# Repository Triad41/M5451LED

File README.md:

# M5451LED is an Arduino Shield with an 8 digit LED display and 14 additional Outputs. It is based on the M5451 40 pin Dip IC. The IC basically works as a shift register with 35 output lines. Each line can sink about 25mA which allows it to directly drive LEDs. 21 Lines are used for the display segments and digit selection in a multiplexed fashion. The additional 14 outputs are available on a 20 postion header allowing expansion of the shield. The shield uses only 2 data lines from the arduino for (clock and data). The M5451.zip file is the Arduino libaray and 2 example programs for the shield. The first is a straight loop approach for updating the display, the second is an itnerrupt based approach for updating the display.

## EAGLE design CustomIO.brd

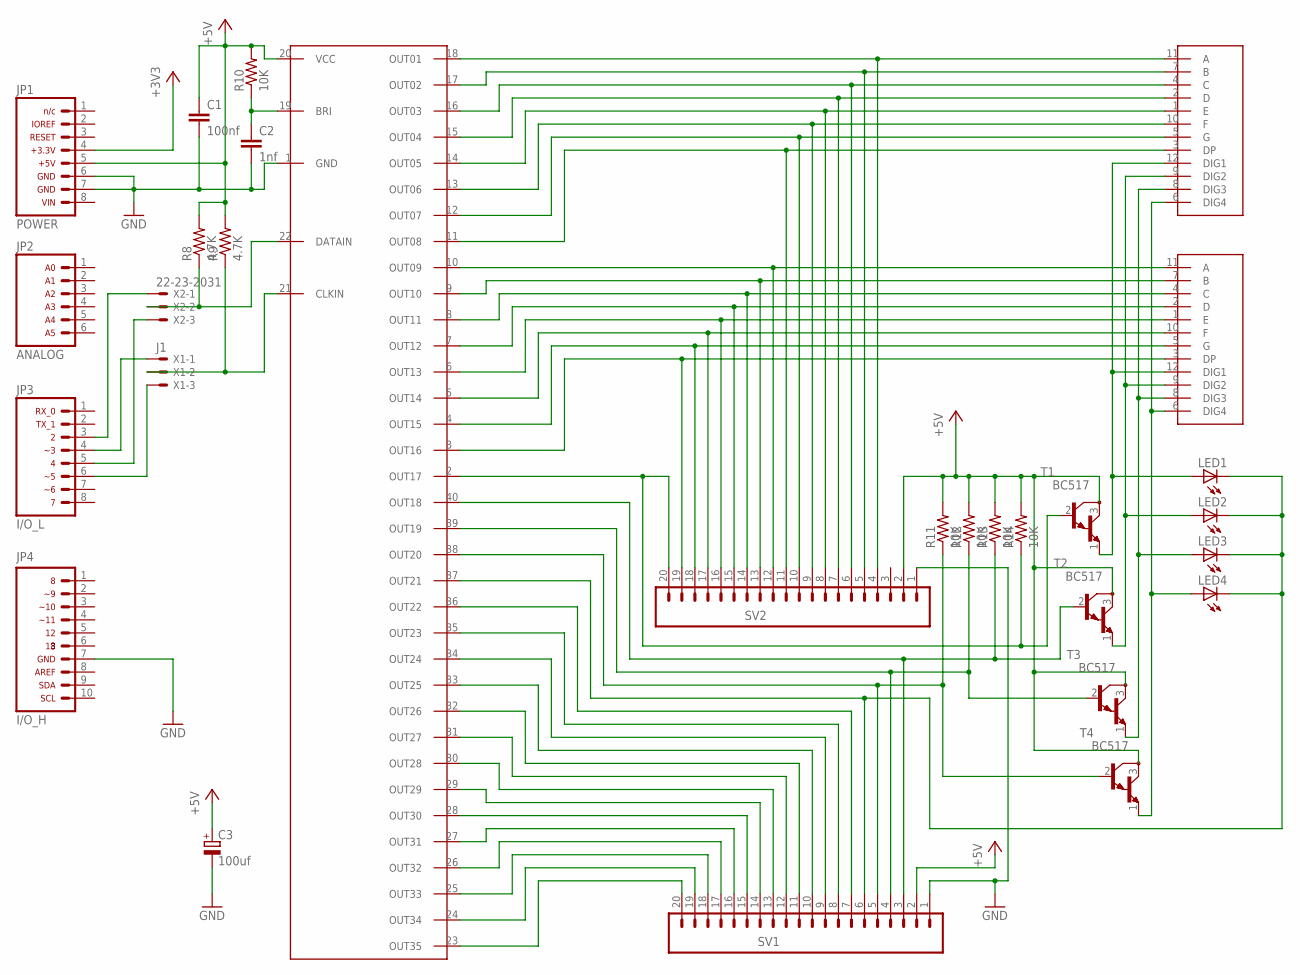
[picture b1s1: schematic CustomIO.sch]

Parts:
C1: 100nf; C2.5-4
C2: 1nf; C5B2.5
C3: 100uf; E2,5-7---100UF
JP1: ARDUINO_CONN-POWERSIP; CONN-1X08
JP2: ARDUINO_CONN-ANALOGSIP; CONN-1X06
JP3: ARDUINO_CONN-IO_LSIP; CONN-1X08
JP4: ARDUINO_CONN-IO_HSIP; CONN-1X10
LED1, LED2, LED3, LED4: LED3MM; HLMP-D105
R8, R9: 4.7K; AXIAL-0.3-KIT
R10, R11, R12, R13, R14: 10K; AXIAL-0.3-KIT
SV1, SV2: MA10-2
T1, T2, T3, T4: BC517; TO92
U$1: ST-M5451PDIP40; DIL40
U$2, U$3: LDS-3461BXTHURHOLE; LDS-3461BX
X1: J1; 22-23-2031
X2: 22-23-2031

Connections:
+3V3: JP1.4
+5V: C1.1, C3.+, JP1.5, R8.P$2 (2), R9.P$2 (2), R10.P$2 (2), R11.P$2 (2), R12.P$2 (2), R13.P$2 (2), R14.P$2 (2), SV1.2, SV2.2, T1.3 (C), T2.3 (C), T3.3 (C), T4.3 (C), U$1.20 (VCC)
GND: C1.2, C2.2, C3.-, JP1.6, JP1.7, JP4.7, SV1.1, SV2.1, U$1.1 (GND)
unnamed: SV2.4, U$1.18 (OUT01), U$2.11 (A)
unnamed: SV2.5, U$1.17 (OUT02), U$2.7 (B)
unnamed: SV2.6, U$1.16 (OUT03), U$2.4 (C)
unnamed: SV2.7, U$1.15 (OUT04), U$2.2 (D)
unnamed: SV2.8, U$1.14 (OUT05), U$2.1 (E)
unnamed: SV2.9, U$1.13 (OUT06), U$2.10 (F)
unnamed: SV2.10, U$1.12 (OUT07), U$2.5 (G)
unnamed: SV2.11, U$1.11 (OUT08), U$2.3 (DP)
unnamed: LED4.A, T4.1 (E), U$2.6 (DIG4), U$3.6 (DIG4)
unnamed: LED3.A, T3.1 (E), U$2.8 (DIG3), U$3.8 (DIG3)
unnamed: LED2.A, T2.1 (E), U$2.9 (DIG2), U$3.9 (DIG2)
unnamed: LED1.A, T1.1 (E), U$2.12 (DIG1), U$3.12 (DIG1)
unnamed: SV2.12, U$1.10 (OUT09), U$3.11 (A)
unnamed: SV2.13, U$1.9 (OUT10), U$3.7 (B)
unnamed: SV2.14, U$1.8 (OUT11), U$3.4 (C)
unnamed: SV2.15, U$1.7 (OUT12), U$3.2 (D)
unnamed: SV2.16, U$1.6 (OUT13), U$3.1 (E)
unnamed: SV2.17, U$1.5 (OUT14), U$3.10 (F)
unnamed: SV2.18, U$1.4 (OUT15), U$3.5 (G)
unnamed: SV2.19, U$1.3 (OUT16), U$3.3 (DP)
unnamed: SV1.20, U$1.23 (OUT35)
unnamed: SV1.19, U$1.24 (OUT34)
unnamed: SV1.18, U$1.25 (OUT33)
unnamed: SV1.17, U$1.26 (OUT32)
unnamed: SV1.16, U$1.27 (OUT31)
unnamed: SV1.15, U$1.28 (OUT30)
unnamed: SV1.14, U$1.29 (OUT29)
unnamed: SV1.13, U$1.30 (OUT28)
unnamed: SV1.12, U$1.31 (OUT27)
unnamed: SV1.11, U$1.32 (OUT26)
unnamed: SV1.10, U$1.33 (OUT25)
unnamed: SV1.9, U$1.34 (OUT24)
unnamed: SV1.8, U$1.35 (OUT23)
unnamed: SV1.7, U$1.36 (OUT22)
unnamed: LED1.K (C), LED2.K (C), LED3.K (C), LED4.K (C), SV1.6, U$1.37 (OUT21)
unnamed: R11.P$1 (1), SV1.5, T4.2 (B), U$1.38 (OUT20)
unnamed: R12.P$1 (1), SV1.4, T3.2 (B), U$1.39 (OUT19)
unnamed: R13.P$1 (1), SV1.3, T2.2 (B), U$1.40 (OUT18)
unnamed: R14.P$1 (1), SV2.20, T1.2 (B), U$1.2 (OUT17)
unnamed: R9.P$1 (1), U$1.21 (CLKIN), X1.2
unnamed: C2.1, R10.P$1 (1), U$1.19 (BRI)
unnamed: R8.P$1 (1), U$1.22 (DATAIN), X2.2
unnamed: JP3.3, X2.1
unnamed: JP3.4, X1.1
unnamed: JP3.5, X2.3
unnamed: JP3.6, X1.3

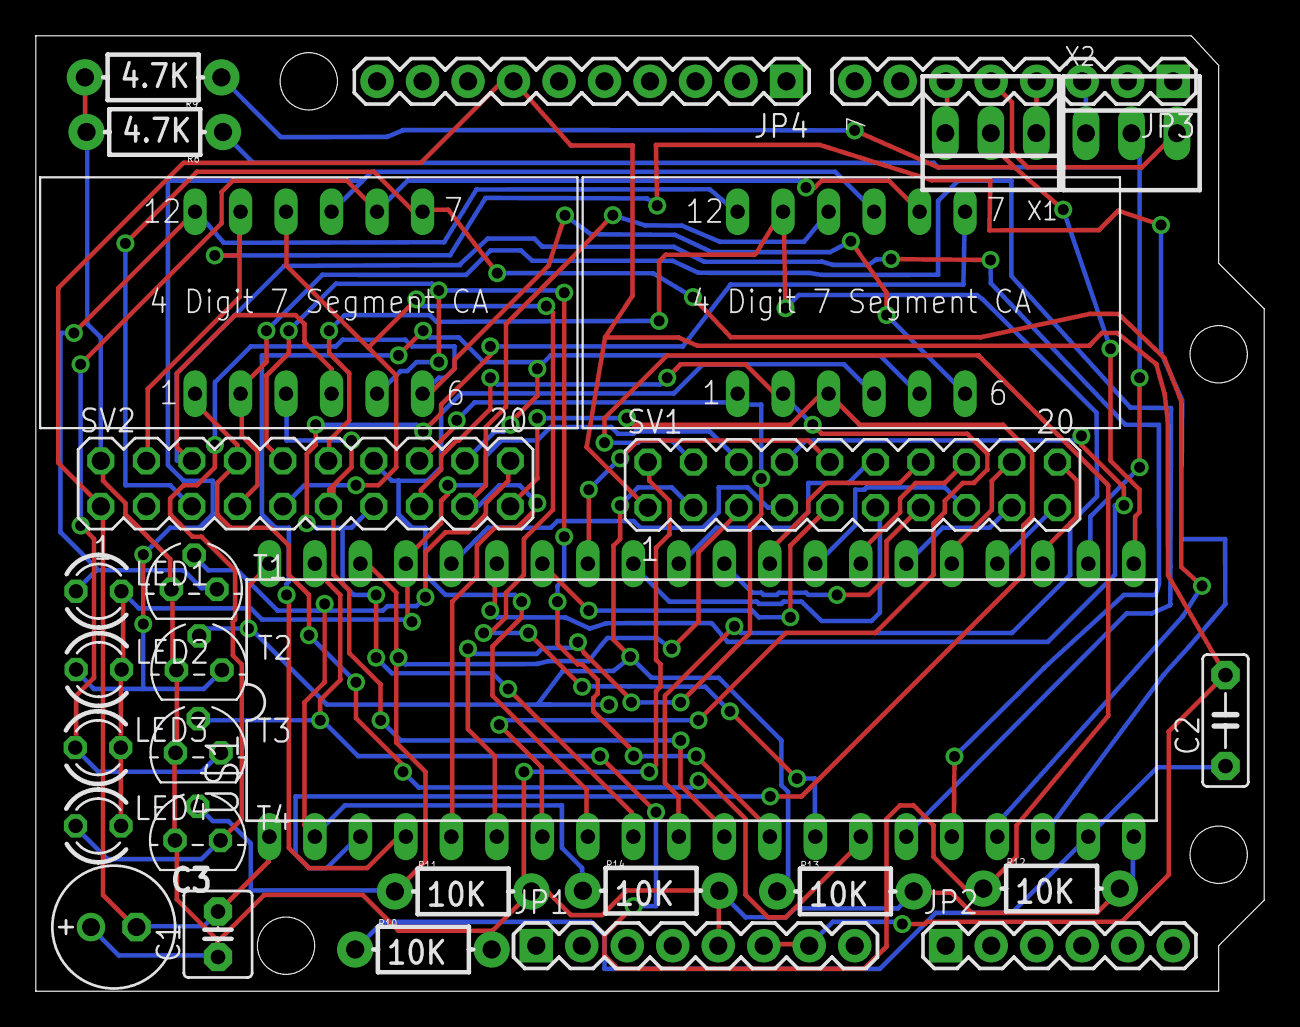
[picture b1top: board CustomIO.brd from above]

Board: 2 copper layers, 68.6 x 53.3 mm, 29 parts (0 on the bottom side), 48 nets.

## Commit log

2016-05-20 M5451LED Board
    M5451LED Board
2016-05-20 M5451LED Schematic
    M5451LED Schematic
2016-05-20 Video of Sample Code Running
    Video of the sample arduino program running on the board. also available on You Tube at
    https://youtu.be/1ersXG6CpGg
    and
    https://youtu.be/Mj3757OHWhI
2016-05-20 PCB Build Instructions
    PCB Build Instructions
2016-05-20 Video of the M5451LED Shield running the sample sketch.
    Video of the M5451LED Shield running the sample sketch.
2016-05-20 Video of the M5451LED Shield running the sample sketch with some extended outputs hooked up.
    Video of the M5451LED Shield running the sample sketch with some extended outputs hooked up.

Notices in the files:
parts and their libraries:
SparkFun-Resistors: Licensing: Creative Commons ShareAlike 4.0 International - https://creativecommons.org/licenses/by-sa/4.0
